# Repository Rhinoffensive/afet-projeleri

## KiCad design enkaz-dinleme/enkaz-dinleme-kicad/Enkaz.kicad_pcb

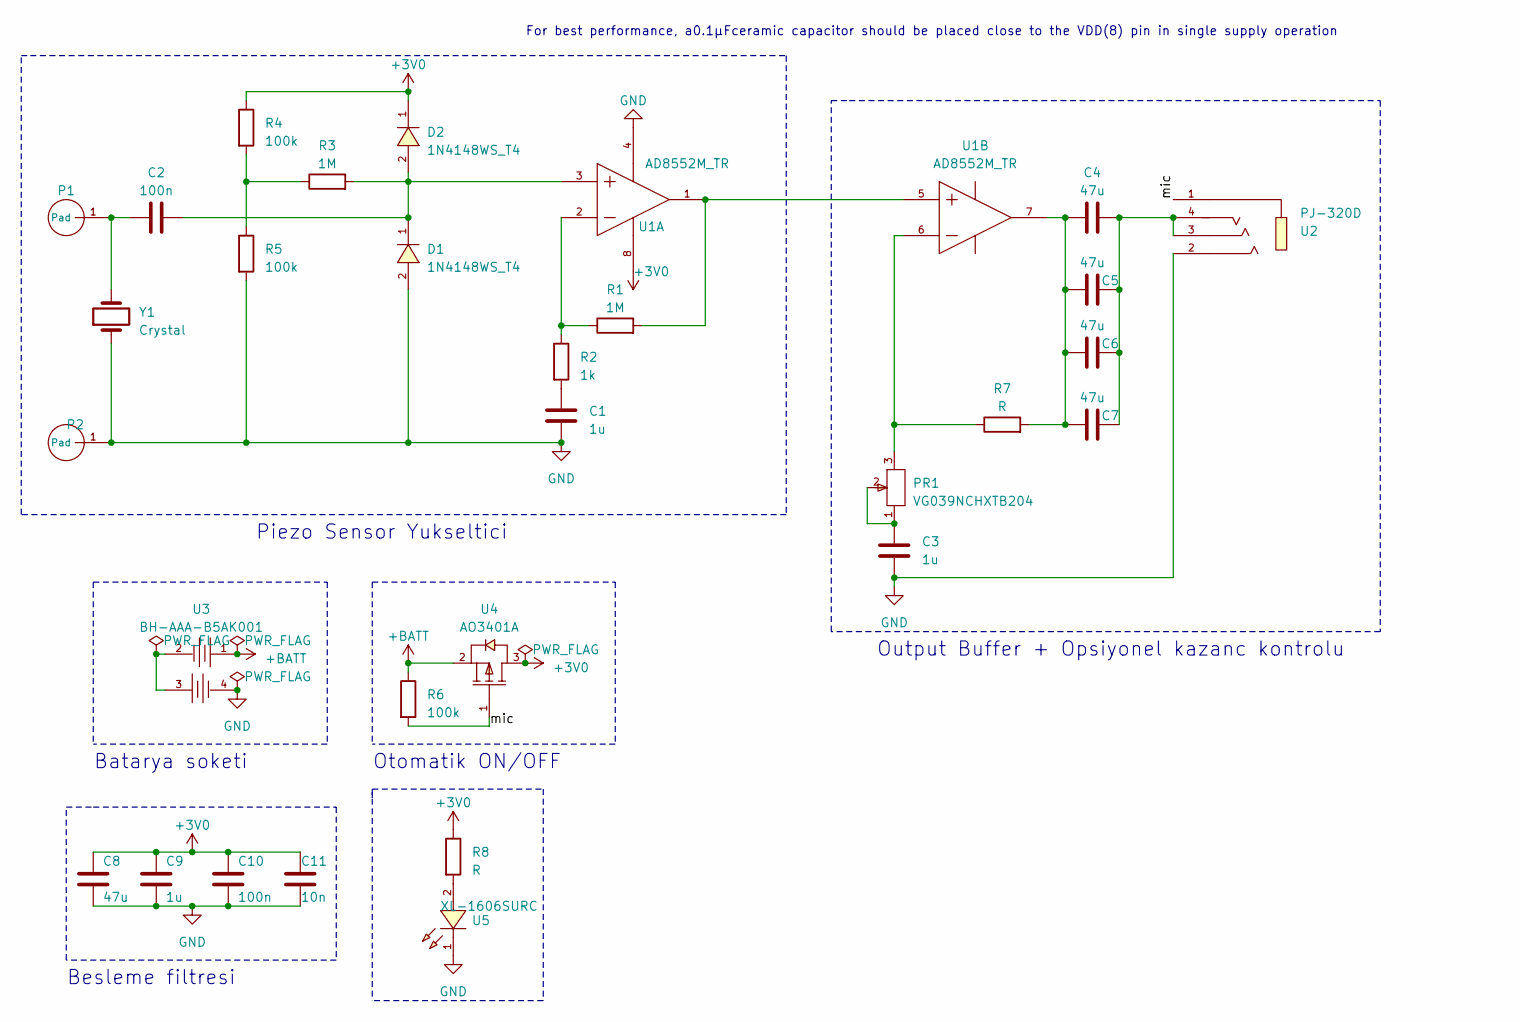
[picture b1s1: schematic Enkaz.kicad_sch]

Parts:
C1, C3, C9: 1u; C_0603_1608Metric_Pad1.08x0.95mm_HandSolder
C2, C10: 100n; C_0603_1608Metric_Pad1.08x0.95mm_HandSolder
C4, C5, C6, C7, C8: 47u; C_0805_2012Metric_Pad1.18x1.45mm_HandSolder
C11: 10n; C_0603_1608Metric_Pad1.08x0.95mm_HandSolder
D1, D2: 1N4148WS_T4; SOD-323_L1.8-W1.3-LS2.5-RD; LCSC C2128
P1, P2: PAD
PR1: VG039NCHXTB204; RES-ADJ-SMD_VG039NCH; LCSC C128551
R1: 1M; C_0603_1608Metric_Pad1.08x0.95mm_HandSolder
R2: 1k; R_0603_1608Metric_Pad0.98x0.95mm_HandSolder
R3: 1M; C_0805_2012Metric_Pad1.18x1.45mm_HandSolder
R4, R5, R6: 100k; R_0603_1608Metric_Pad0.98x0.95mm_HandSolder
R7: R; R_0603_1608Metric_Pad0.98x0.95mm_HandSolder
R8: R; C_0603_1608Metric_Pad1.08x0.95mm_HandSolder
U1: AD8552M_TR; SOP-8_L4.9-W3.9-P1.27-LS6.0-BL; LCSC C356702
U2: PJ-320D; AUDIO-SMD_PJ-320D; LCSC C431535
U3: BH-AAA-B5AK001; BAT-SMD_BH-AAA-B5AA001; LCSC C964882
U4: AO3401A; SOT-23_L2.9-W1.3-P1.90-LS2.4-BR; LCSC C15127
U5: XL-1606SURC; LED-SMD_L1.7-W1.1-RD_RED-SIDE; LCSC C965860
Y1: Crystal; C_0603_1608Metric_Pad1.08x0.95mm_HandSolder

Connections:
+3V0: C8.1, C9.1, C10.1, C11.1, D2.1 (K), R4.1, R8.1, U1.8 (VDD), U4.3 (D)
+BATT: R6.1, U3.1, U4.2 (S)
/mic: R6.2, U2.1, U4.1 (G)
GND: C1.2, C3.1, C8.2, C9.2, C10.2, C11.2, D1.2 (A), P2.1 (Pad), R5.2, U1.4 (VSS), U2.2, U3.4, U5.1 (K), Y1.1
unnamed: C1.1, R2.2
unnamed: C2.1, P1.1 (Pad), Y1.2
unnamed: C3.2, PR1.1, PR1.2
unnamed: C4.2, C5.2, C6.2, C7.1, U2.3, U2.4
unnamed: C2.2, D1.1 (K), D2.2 (A), R3.2, U1.3 (INA+)
unnamed: R3.1, R4.2, R5.1
unnamed: R1.1, R2.1, U1.2 (INA-)
unnamed: R1.2, U1.1 (OUTA), U1.5 (INB+)
unnamed: PR1.3, R7.1, U1.6 (INB-)
unnamed: C4.1, C5.1, C6.1, C7.2, R7.2, U1.7 (OUTB)
unnamed: U3.2, U3.3
unnamed: R8.2, U5.2 (A)

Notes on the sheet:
Output Buffer + Opsiyonel kazanc kontrolu
For best performance, a0.1µFceramic capacitor should be placed close to the VDD(8) pin in single supply operation
Besleme filtresi
Piezo Sensor Yukseltici
Otomatik ON/OFF
Batarya soketi

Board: 2 copper layers, 30 parts (0 on the bottom side), 16 nets, no tracks yet.

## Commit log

2023-03-26 Kicad init
2023-03-29 3d models add, rough layout
